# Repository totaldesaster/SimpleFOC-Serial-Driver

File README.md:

# SimpleFOC-Serial-Driver
Advanced dual BLDC driver modules, designed to be controlled from a trajectory controller over a serial connection. Features a compact high power design with two stacked PCBs. While the top PCB focuses on motor driving, the bottom PCB serves as the controller and interface board.

Work in Progress, will be updated as more information and tests become available!

# Base Board (RP2350)

The base board acts as a carrier for power boards and contains the microcontroller, communications and programming interfaces, and power input circuits. It shares power with top-mounted driver boards over the standoffs in the mounting holes. It's equipped with:  

- RP2354B, Dual Cortex-M33 or RISC-V processors at 150MHz
- THVD1424, communication over RS-485 or RS-422 at up to 10MHz
- Input voltage and current monitoring
- Two Encoder connections with I2C interfaces
- External connections to power, RS-422/485 and TTL UART

# Dual BLDC driver board

Featuring two BLDC drivers and an auxiliary circuit to dissipate braking energy, the Dual BLDC board is able to drive low to medium power BLDCs at up to 7 amps. Peak currents may be far higher (not yet tested).  

- Two DRV8323S (SPI configuration) or DRV8323H (hard-coded) BLDC drivers
- Medium-Power HSBB6066 MOSFETs
- Onboard brake resistor able to dissipate ~5 watts
- Onboard thermistor to measure the board's temperature

# High-Power BLDC driver board

Equipped with bigger MOSFETs and connection points for an external brake resistor and power supply, this board is able to drive a much higher power motor.  

- DRV8323S BLDC driver
- 160A rated Infineon OptiMOS MOSFETs, continuous power limited by thermals (not yet tested)$
- Auxiliary output for external brake resistor
- Onboard thermistor to measure the board's temperature

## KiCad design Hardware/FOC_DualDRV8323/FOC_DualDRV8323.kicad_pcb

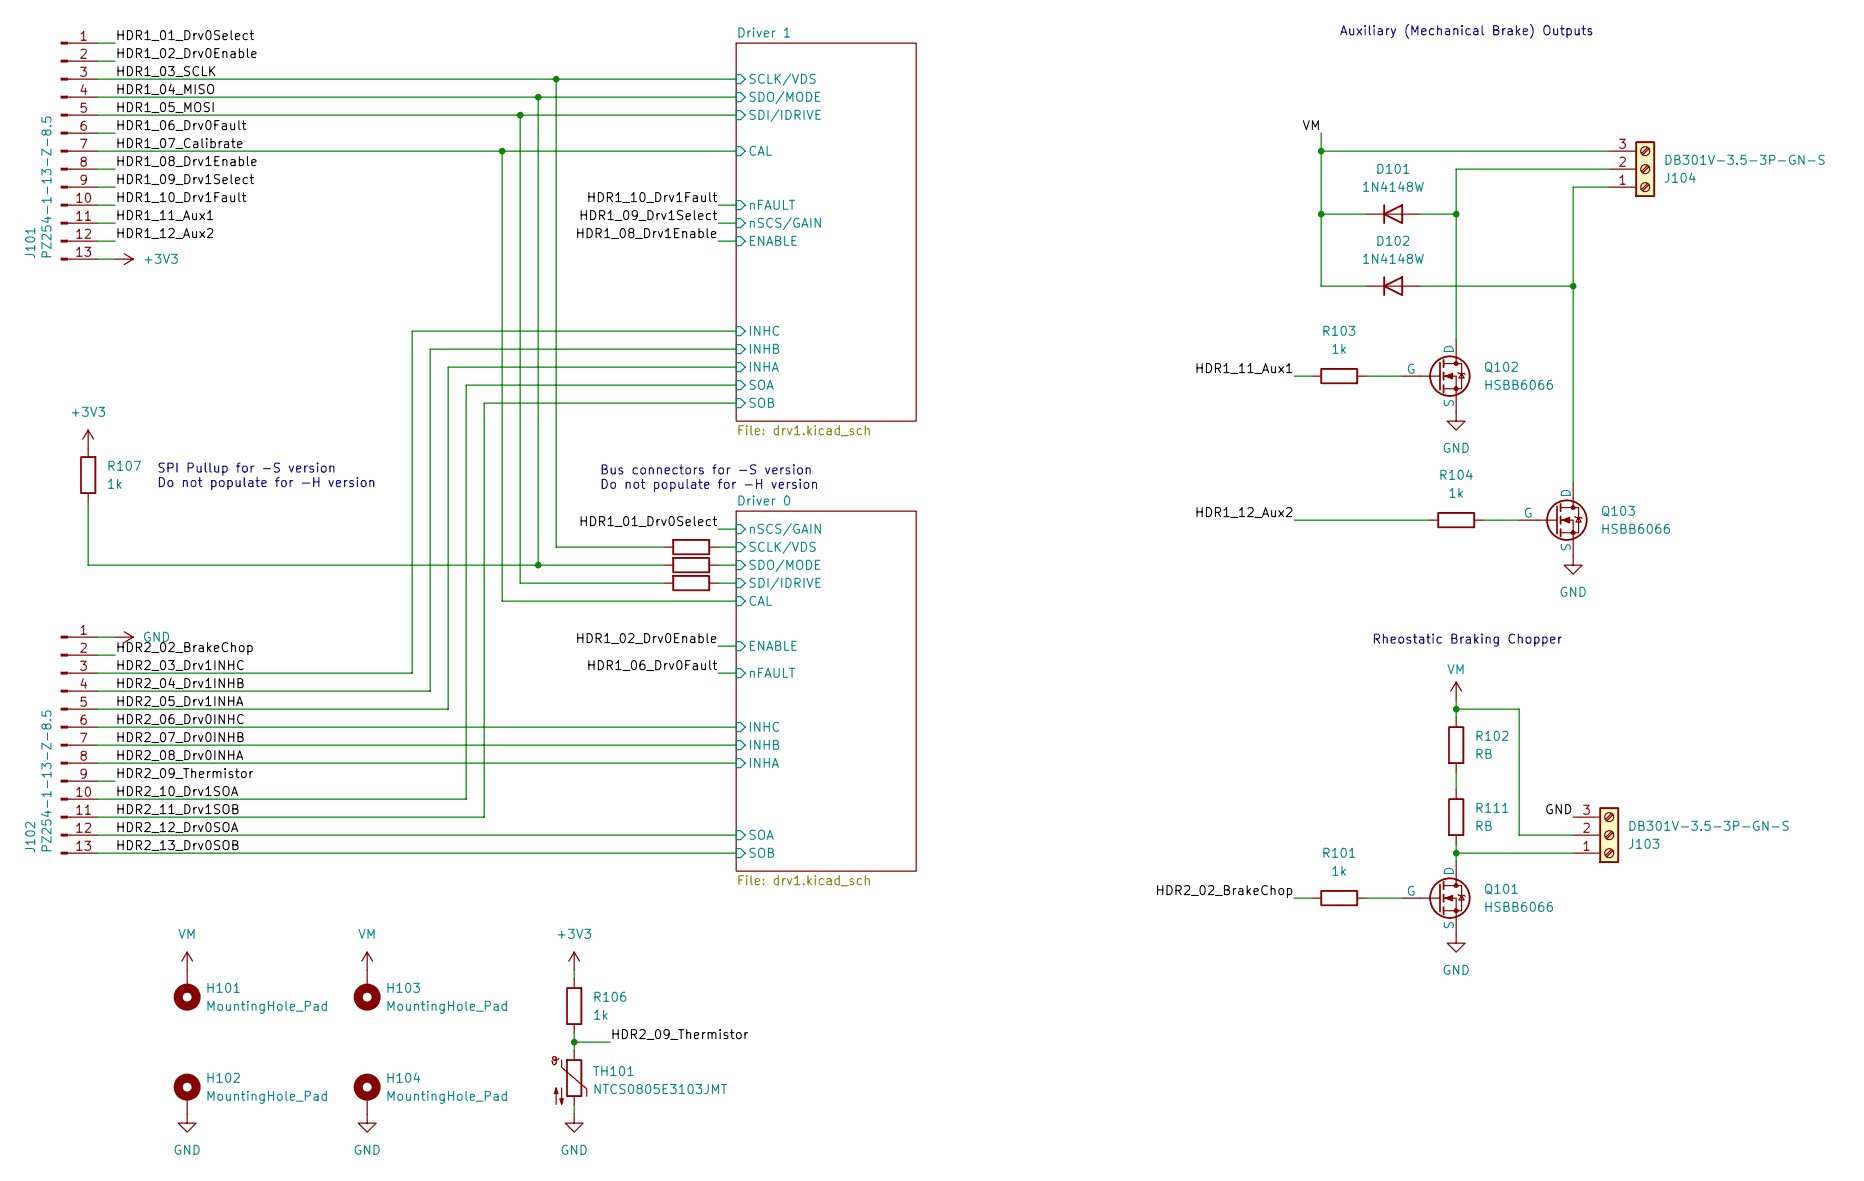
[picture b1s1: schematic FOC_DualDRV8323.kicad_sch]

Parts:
D101, D102: 1N4148W; D_SOD-123
H101, H102, H103, H104: MountingHole_Pad; MountingHole_3.2mm_M3_Pad_Via
J101: PZ254-1-13-Z-8.5; PinHeader_1x13_P2.54mm_Vertical_SMD_Pin1Left
J102: PZ254-1-13-Z-8.5; PinHeader_1x13_P2.54mm_Vertical_SMD_Pin1Right
J103, J104: DB301V-3.5-3P-GN-S; TerminalBlock_Phoenix_PT-1,5-3-3.5-H_1x03_P3.50mm_Horizontal
Q101, Q102, Q103: HSBB6066; VSON-8_3.3x3.3mm_P0.65mm_NexFET
R101, R103, R104, R106, R107: 1k; R_0603_1608Metric
R102, R111: RB; R_Axial_DIN0414_L11.9mm_D4.5mm_P15.24mm_Horizontal
R108, R109, R110: 0; R_0603_1608Metric
TH101: NTCS0805E3103JMT; R_0805_2012Metric

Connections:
+3V3: J101.13, R106.2, R107.2
/Driver 0/SCLK/VDS: R108.1; also elsewhere on the board
/Driver 0/SDI/IDRIVE: R110.1; also elsewhere on the board
/Driver 0/SDO/MODE: R109.1; also elsewhere on the board
/HDR1_01_Drv0Select: J101.1; also elsewhere on the board
/HDR1_02_Drv0Enable: J101.2; also elsewhere on the board
/HDR1_03_SCLK: J101.3, R108.2; also elsewhere on the board
/HDR1_04_MISO: J101.4, R107.1, R109.2; also elsewhere on the board
/HDR1_05_MOSI: J101.5, R110.2; also elsewhere on the board
/HDR1_06_Drv0Fault: J101.6; also elsewhere on the board
/HDR1_07_Calibrate: J101.7; also elsewhere on the board
/HDR1_08_Drv1Enable: J101.8; also elsewhere on the board
/HDR1_09_Drv1Select: J101.9; also elsewhere on the board
/HDR1_10_Drv1Fault: J101.10; also elsewhere on the board
/HDR1_11_Aux1: J101.11, R103.1
/HDR1_12_Aux2: J101.12, R104.1
/HDR2_02_BrakeChop: J102.2, R101.1
/HDR2_03_Drv1INHC: J102.3; also elsewhere on the board
/HDR2_04_Drv1INHB: J102.4; also elsewhere on the board
/HDR2_05_Drv1INHA: J102.5; also elsewhere on the board
/HDR2_06_Drv0INHC: J102.6; also elsewhere on the board
/HDR2_07_Drv0INHB: J102.7; also elsewhere on the board
/HDR2_08_Drv0INHA: J102.8; also elsewhere on the board
/HDR2_09_Thermistor: J102.9, R106.1, TH101.1
/HDR2_10_Drv1SOA: J102.10; also elsewhere on the board
/HDR2_11_Drv1SOB: J102.11; also elsewhere on the board
/HDR2_12_Drv0SOA: J102.12; also elsewhere on the board
/HDR2_13_Drv0SOB: J102.13; also elsewhere on the board
GND: H102.1 (1_1), H104.1 (1_1), J102.1, J103.3, Q101.3 (S), Q102.3 (S), Q103.3 (S), TH101.2; also elsewhere on the board
unnamed: D101.2 (A), J104.2, Q102.1 (D)
unnamed: D102.2 (A), J104.1, Q103.1 (D)
unnamed: J103.1, Q101.1 (D), R111.2
unnamed: Q101.2 (G), R101.2
unnamed: Q102.2 (G), R103.2
unnamed: Q103.2 (G), R104.2
unnamed: R102.2, R111.1
VM: D101.1 (K), D102.1 (K), H101.1 (1_1), H103.1 (1_1), J103.2, J104.3, R102.1; also elsewhere on the board

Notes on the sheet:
Rheostatic Braking Chopper
Bus connectors for -S version Do not populate for -H version
Auxiliary (Mechanical Brake) Outputs
SPI Pullup for -S version Do not populate for -H version

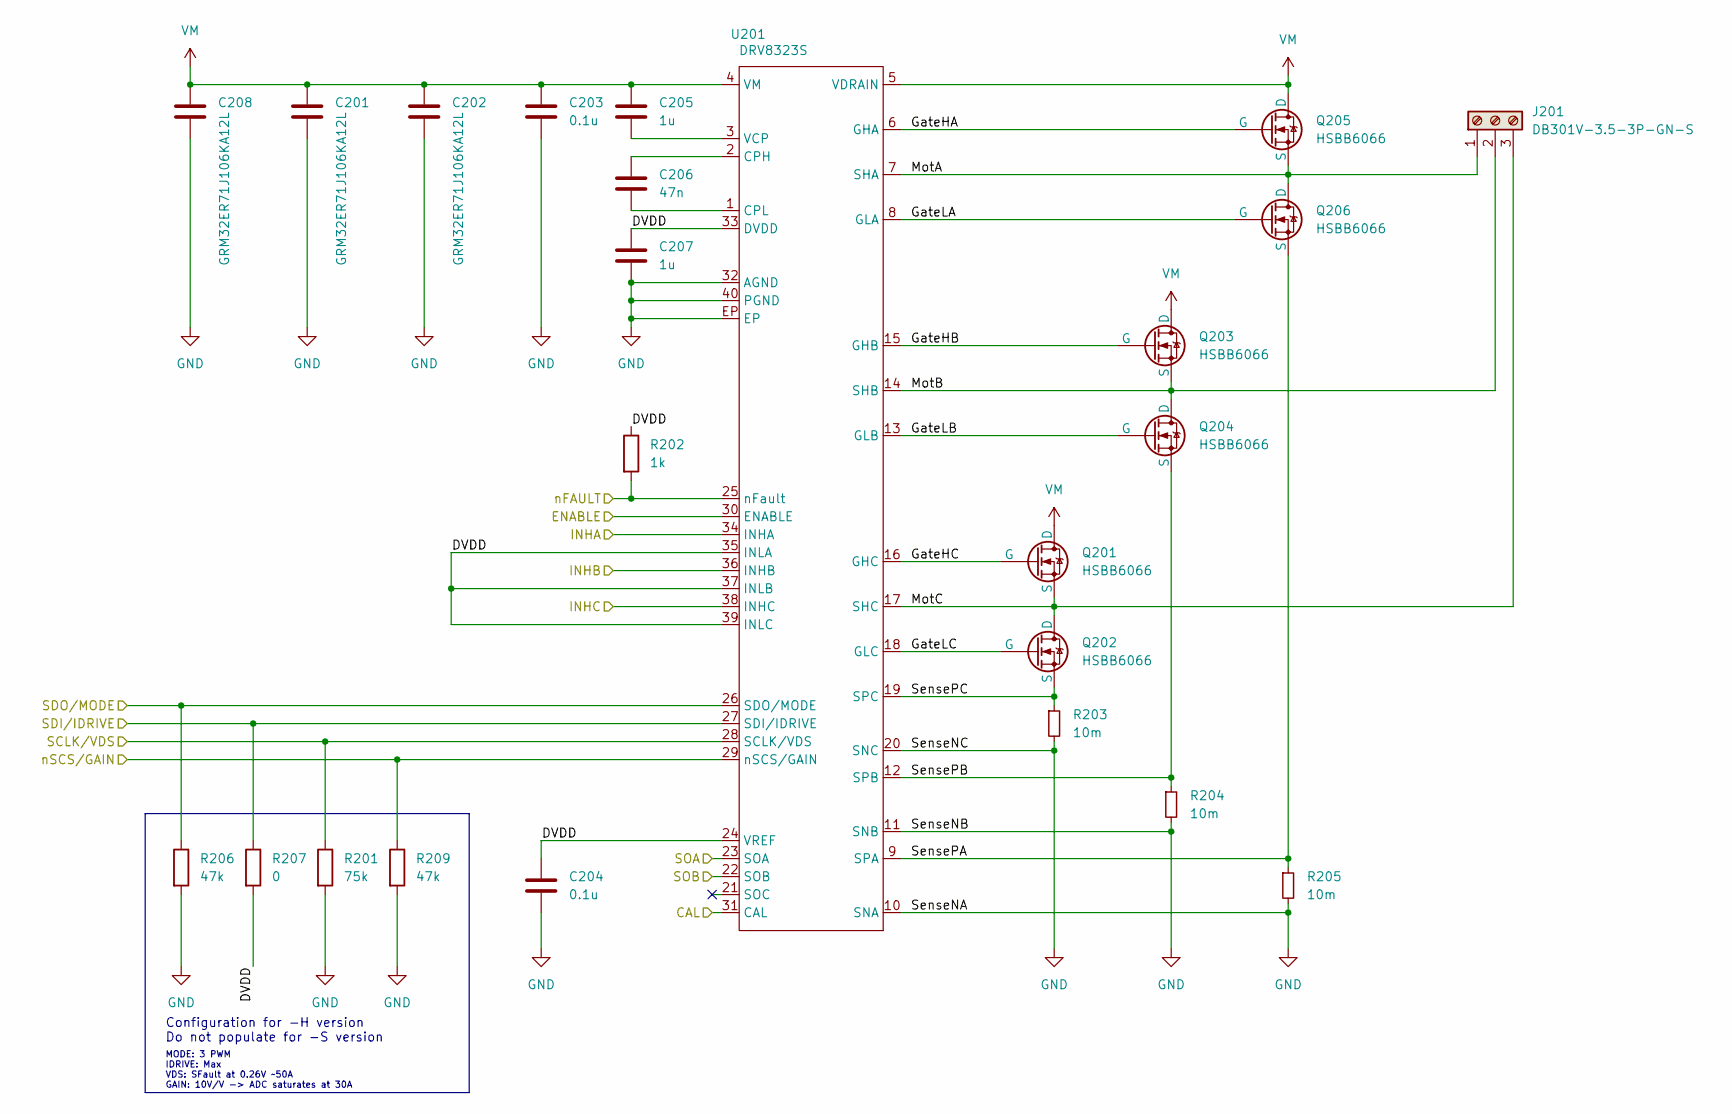
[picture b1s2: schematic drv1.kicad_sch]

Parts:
C201, C202, C208: GRM32ER71J106KA12L; C_1210_3225Metric
C203, C204: 0.1u; C_0603_1608Metric
C205, C207: 1u; C_0603_1608Metric
C206: 47n; C_0603_1608Metric
J201: DB301V-3.5-3P-GN-S; TerminalBlock_Phoenix_PT-1,5-3-3.5-H_1x03_P3.50mm_Horizontal
Q201, Q202, Q203, Q204, Q205, Q206: HSBB6066; VSON-8_3.3x3.3mm_P0.65mm_NexFET
R201: 75k; R_0603_1608Metric
R202: 1k; R_0603_1608Metric
R203, R204, R205: 10m; R_1206_3216Metric
R206, R209: 47k; R_0603_1608Metric
R207: 0; R_0603_1608Metric
U201: DRV8323S; Texas_RHA0040E_VQFN-40-1EP_6x6mm_P0.5mm_EP3.52x2.62mm

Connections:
/Driver 0/DVDD: C204.1, C207.1, R202.1, R207.2, U201.24 (VREF), U201.33 (DVDD), U201.35 (INLA), U201.37 (INLB), U201.39 (INLC)
/Driver 0/GateHA: Q205.2 (G), U201.6 (GHA)
/Driver 0/GateHB: Q203.2 (G), U201.15 (GHB)
/Driver 0/GateHC: Q201.2 (G), U201.16 (GHC)
/Driver 0/GateLA: Q206.2 (G), U201.8 (GLA)
/Driver 0/GateLB: Q204.2 (G), U201.13 (GLB)
/Driver 0/GateLC: Q202.2 (G), U201.18 (GLC)
/Driver 0/MotA: J201.1, Q205.3 (S), Q206.1 (D), U201.7 (SHA)
/Driver 0/MotB: J201.2, Q203.3 (S), Q204.1 (D), U201.14 (SHB)
/Driver 0/MotC: J201.3, Q201.3 (S), Q202.1 (D), U201.17 (SHC)
/Driver 0/SCLK/VDS: R201.1, U201.28 (SCLK/VDS); also elsewhere on the board
/Driver 0/SDI/IDRIVE: R207.1, U201.27 (SDI/IDRIVE); also elsewhere on the board
/Driver 0/SDO/MODE: R206.1, U201.26 (SDO/MODE); also elsewhere on the board
/Driver 0/SensePA: Q206.3 (S), R205.1, U201.9 (SPA)
/Driver 0/SensePB: Q204.3 (S), R204.1, U201.12 (SPB)
/Driver 0/SensePC: Q202.3 (S), R203.1, U201.19 (SPC)
/HDR1_01_Drv0Select: R209.1, U201.29 (nSCS/GAIN); also elsewhere on the board
/HDR1_02_Drv0Enable: U201.30 (ENABLE); also elsewhere on the board
/HDR1_06_Drv0Fault: R202.2, U201.25 (nFault); also elsewhere on the board
/HDR1_07_Calibrate: U201.31 (CAL); also elsewhere on the board
/HDR2_06_Drv0INHC: U201.38 (INHC); also elsewhere on the board
/HDR2_07_Drv0INHB: U201.36 (INHB); also elsewhere on the board
/HDR2_08_Drv0INHA: U201.34 (INHA); also elsewhere on the board
/HDR2_12_Drv0SOA: U201.23 (SOA); also elsewhere on the board
/HDR2_13_Drv0SOB: U201.22 (SOB); also elsewhere on the board
GND: C201.2, C202.2, C203.2, C204.2, C207.2, C208.2, R201.2, R203.2, R204.2, R205.2, R206.2, R209.2, U201.10 (SNA), U201.11 (SNB), U201.20 (SNC), U201.32 (AGND), U201.40 (PGND), U201.EP; also elsewhere on the board
unnamed: C206.1, U201.2 (CPH)
unnamed: C206.2, U201.1 (CPL)
unnamed: C205.2, U201.3 (VCP)
VM: C201.1, C202.1, C203.1, C205.1, C208.1, Q201.1 (D), Q203.1 (D), Q205.1 (D), U201.4 (VM), U201.5 (VDRAIN); also elsewhere on the board

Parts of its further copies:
C301, C302, C308: GRM32ER71J106KA12L; C_1210_3225Metric
C303, C304: 0.1u; C_0603_1608Metric
C305, C307: 1u; C_0603_1608Metric
C306: 47n; C_0603_1608Metric
J301: DB301V-3.5-3P-GN-S; TerminalBlock_Phoenix_PT-1,5-3-3.5-H_1x03_P3.50mm_Horizontal
Q301, Q302, Q303, Q304, Q305, Q306: HSBB6066; VSON-8_3.3x3.3mm_P0.65mm_NexFET
R301: 75k; R_0603_1608Metric
R302: 1k; R_0603_1608Metric
R303, R304, R305: 10m; R_1206_3216Metric
R306, R309: 47k; R_0603_1608Metric
R307: 0; R_0603_1608Metric
U301: DRV8323S; Texas_RHA0040E_VQFN-40-1EP_6x6mm_P0.5mm_EP3.52x2.62mm

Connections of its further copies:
/Driver 1/DVDD: C304.1, C307.1, R302.1, R307.2, U301.24 (VREF), U301.33 (DVDD), U301.35 (INLA), U301.37 (INLB), U301.39 (INLC)
/Driver 1/GateHA: Q305.2 (G), U301.6 (GHA)
/Driver 1/GateHB: Q303.2 (G), U301.15 (GHB)
/Driver 1/GateHC: Q301.2 (G), U301.16 (GHC)
/Driver 1/GateLA: Q306.2 (G), U301.8 (GLA)
/Driver 1/GateLB: Q304.2 (G), U301.13 (GLB)
/Driver 1/GateLC: Q302.2 (G), U301.18 (GLC)
/Driver 1/MotA: J301.1, Q305.3 (S), Q306.1 (D), U301.7 (SHA)
/Driver 1/MotB: J301.2, Q303.3 (S), Q304.1 (D), U301.14 (SHB)
/Driver 1/MotC: J301.3, Q301.3 (S), Q302.1 (D), U301.17 (SHC)
/Driver 1/SensePA: Q306.3 (S), R305.1, U301.9 (SPA)
/Driver 1/SensePB: Q304.3 (S), R304.1, U301.12 (SPB)
/Driver 1/SensePC: Q302.3 (S), R303.1, U301.19 (SPC)
/HDR1_03_SCLK: R301.1, U301.28 (SCLK/VDS); also elsewhere on the board
/HDR1_04_MISO: R306.1, U301.26 (SDO/MODE); also elsewhere on the board
/HDR1_05_MOSI: R307.1, U301.27 (SDI/IDRIVE); also elsewhere on the board
/HDR1_07_Calibrate: U301.31 (CAL); also elsewhere on the board
/HDR1_08_Drv1Enable: U301.30 (ENABLE); also elsewhere on the board
/HDR1_09_Drv1Select: R309.1, U301.29 (nSCS/GAIN); also elsewhere on the board
/HDR1_10_Drv1Fault: R302.2, U301.25 (nFault); also elsewhere on the board
/HDR2_03_Drv1INHC: U301.38 (INHC); also elsewhere on the board
/HDR2_04_Drv1INHB: U301.36 (INHB); also elsewhere on the board
/HDR2_05_Drv1INHA: U301.34 (INHA); also elsewhere on the board
/HDR2_10_Drv1SOA: U301.23 (SOA); also elsewhere on the board
/HDR2_11_Drv1SOB: U301.22 (SOB); also elsewhere on the board
GND: C301.2, C302.2, C303.2, C304.2, C307.2, C308.2, R301.2, R303.2, R304.2, R305.2, R306.2, R309.2, U301.10 (SNA), U301.11 (SNB), U301.20 (SNC), U301.32 (AGND), U301.40 (PGND); also elsewhere on the board
unnamed: C306.1, U301.2 (CPH)
unnamed: C306.2, U301.1 (CPL)
unnamed: C305.2, U301.3 (VCP)
VM: C301.1, C302.1, C303.1, C305.1, C308.1, Q301.1 (D), Q303.1 (D), Q305.1 (D), U301.4 (VM), U301.5 (VDRAIN); also elsewhere on the board

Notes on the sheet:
Configuration for -H version Do not populate for -S version
MODE: 3 PWM IDRIVE: Max VDS: SFault at 0.26V ~50A GAIN: 10V/V -> ADC saturates at 30A

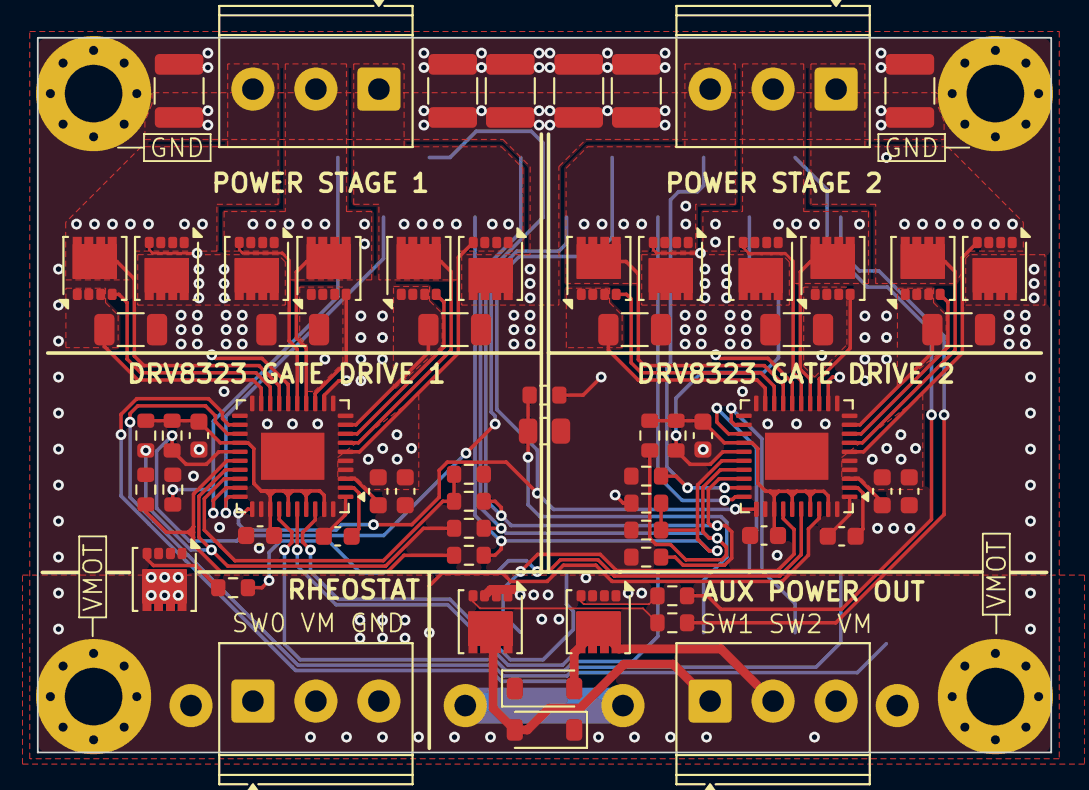
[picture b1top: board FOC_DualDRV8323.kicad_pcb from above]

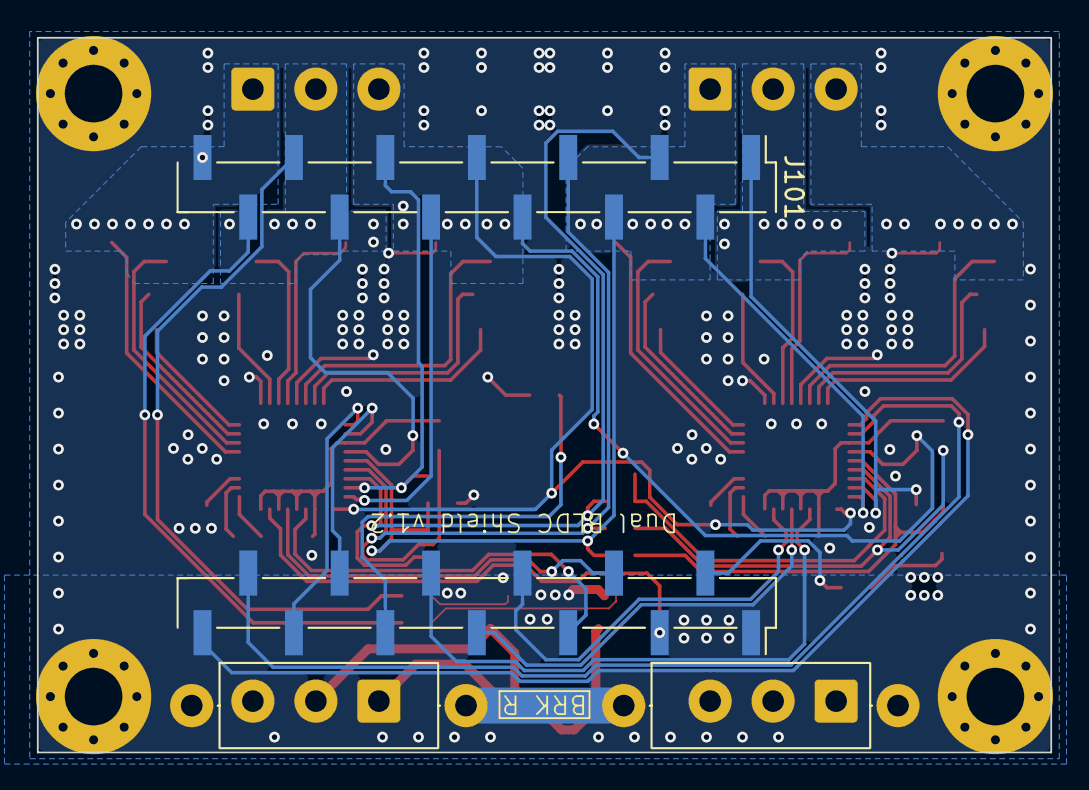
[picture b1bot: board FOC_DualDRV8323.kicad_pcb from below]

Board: 4 copper layers, 56.3 x 39.7 mm, 72 parts (4 on the bottom side), 69 nets.

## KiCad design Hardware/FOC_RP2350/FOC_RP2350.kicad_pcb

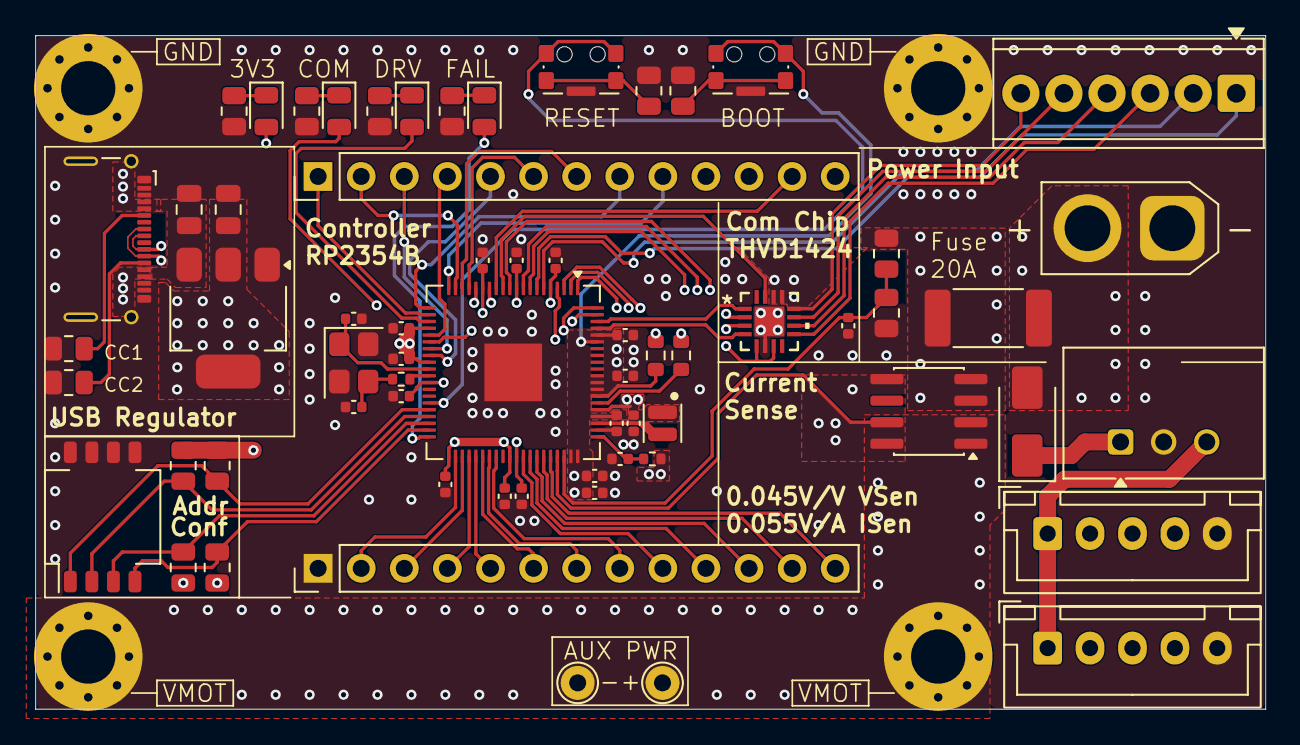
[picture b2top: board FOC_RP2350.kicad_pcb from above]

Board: 4 copper layers, 72.5 x 39.7 mm, 68 parts (0 on the bottom side), 78 nets.

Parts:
C201, C202, C203, C204, C205, C206, C208, C209, C211, C213, C214, C215, C216: 100n; C_0402_1005Metric
C207, C210, C212, C403: 4.7u; C_0402_1005Metric
C217, C218: 15p; C_0402_1005Metric
C401, C402: 22u; C_0805_2012Metric
D301, D302, D303: KT-0805G; LED_0805_2012Metric
D304: KT-0805R; LED_0805_2012Metric
D401: SS12; D_SMA
F401: BSMD2410C-2200T; Fuse_2512_6332Metric_Pad1.52x3.35mm_HandSolder
H401, H402, H403, H404: MountingHole_Pad; MountingHole_3.2mm_M3_Pad_Via
H405, H406: MountingHole_Pad; TestPoint_THTPad_D2.0mm_Drill1.0mm
J401: GT-USB-7025; USB_C_Receptacle_G-Switch_GT-USB-7025
J402: DB125-2.54-6P-GN-S; TerminalBlock_Phoenix_MPT-0,5-6-2.54_1x06_P2.54mm_Horizontal
J403, J408: Conn_01x05; JST_XH_B5B-XH-A_1x05_P2.50mm_Vertical
J404: XT30U-M; AMASS_XT30U-F_1x02_P5.0mm_Vertical
J406, J407: PZ254-1-13-Z-8.5; PinHeader_1x13_P2.54mm_Vertical
L201: AOTA-B201610S3R3-101-T; L_Changjiang_FTC201607S
R201: 33; R_0402_1005Metric
R202, R205, R301, R302, R303, R308: 1k; R_0805_2012Metric
R203, R204: 27; R_0603_1608Metric
R206: 1k; R_0402_1005Metric
R304, R305, R306, R307, R401, R402: 5.1k; R_0805_2012Metric
R403: 10k; R_0805_2012Metric
R404: 470; R_0805_2012Metric
SW201, SW202: KMS231GLFS; SW_SPST_CK_KMS2xxGP
SW301: DSHP04TSGER; SW_DIP_SPSTx04_Slide_KingTek_DSHP04TS_W7.62mm_P1.27mm
U201: RP2354B; QFN-80-1EP_10x10mm_P0.4mm_EP3.4x3.4mm
U301: THVD1424RGTR; QFN_24RGTR_TEX
U401: AMS1117-3.3; SOT-223-3_TabPin2
U402: ACS711KLCTR-25AB-T; SOIC-8_3.9x4.9mm_P1.27mm
U403: TSR1-2433E; Converter_DCDC_TRACO_TSR1-xxxxE_THT
Y201: ABM8-272-T3; Crystal_SMD_Abracon_ABM8G-4Pin_3.2x2.5mm

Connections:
/Comms/3V3: C202.1, C204.1, C206.1, C208.1, C209.1, C210.1, C211.1, C213.1, C214.1, C215.1, C216.1, C402.1, D303.2 (A), J403.1, J406.13, J408.1, R201.1, R304.2, R305.2, R306.2, R307.2, U201.5 (IOVDD), U201.15 (IOVDD), U201.24 (IOVDD), U201.29 (IOVDD), U201.41 (IOVDD), U201.50 (IOVDD), U201.59 (ADC_AVDD), U201.60 (IOVDD), U201.64 (VREG_VIN), U201.68 (USB_OTP_VDD), U201.69 (QSPI_IOVDD), U201.76 (IOVDD), U301.13 (VIO), U301.14 (VCC), U401.2 (VO), U402.8 (VCC), U403.3 (Vout)
/Comms/ComBus_HF: U201.12 (GPIO13), U301.15 (H/F)
/Comms/ConfSw_1: R307.1, SW301.1, U201.36 (GPIO28)
/Comms/ConfSw_2: R306.1, SW301.2, U201.37 (GPIO29)
/Comms/ConfSw_3: R305.1, SW301.3, U201.38 (GPIO30)
/Comms/ConfSw_4: R304.1, SW301.4, U201.39 (GPIO31)
/Comms/Led1: D302.2 (A), U201.26 (GPIO25)
/Comms/Led2: D301.2 (A), U201.23 (GPIO23)
/Comms/Led3: D304.2 (A), U201.40 (GPIO32)
/Comms/RS485_A: J402.6, U301.12 (A)
/Comms/RS485_B: J402.5, U301.11 (B)
/Comms/RS485_Y: J402.3, U301.9 (Y)
/Comms/RS485_Z: J402.4, U301.10 (Z)
/Controller/1V1: C201.1, C203.1, C205.1, C207.1, L201.1, U201.10 (DVDD), U201.32 (DVDD), U201.51 (DVDD), U201.65 (VREG_FB)
/Controller/GPIO6: J408.4, U201.3 (GPIO6)
/Controller/GPIO7: J403.4, U201.4 (GPIO7)
/Controller/GPIO14: J406.12, U201.13 (GPIO14)
/Controller/GPIO15: J406.11, U201.14 (GPIO15)
/Controller/GPIO16: J406.10, U201.16 (GPIO16)
/Controller/GPIO17: J406.6, U201.17 (GPIO17)
/Controller/GPIO18: J406.7, U201.18 (GPIO18)
/Controller/GPIO19: J406.2, U201.19 (GPIO19)
/Controller/GPIO22: J406.1, U201.22 (GPIO22)
/GPIO0_UART0_TX: U201.77 (GPIO0), U301.4 (D)
/GPIO1_UART0_RX: U201.78 (GPIO1), U301.1 (R)
/GPIO2_I2C1_SDA: J403.2, U201.79 (GPIO2)
/GPIO3_I2C1_SCL: J403.3, U201.80 (GPIO3)
/GPIO4_I2C0_SDA: J408.2, U201.1 (GPIO4)
/GPIO5_I2C0_SCL: J408.3, U201.2 (GPIO5)
/GPIO8_UART1_TX: J402.2, U201.6 (GPIO8)
/GPIO9_UART1_RX: J402.1, U201.7 (GPIO9)
/GPIO10_TERM: U201.8 (GPIO10), U301.5 (TERM_TX), U301.7 (TERM_RX)
/GPIO11_TXEN: U201.9 (GPIO11), U301.3 (DE)
/GPIO12_RXEN: U201.11 (GPIO12), U301.2 (RE)
/GPIO20_UART1_TX: J406.9, U201.20 (GPIO20)
/GPIO21_UART1_RX: J406.8, U201.21 (GPIO21)
/GPIO24_SPI1_MISO: J406.4, U201.25 (GPIO24)
/GPIO26_SPI1_SCK: J406.3, U201.27 (GPIO26)
/GPIO27_SPI1_MOSI: J406.5, U201.28 (GPIO27)
/GPIO33_PWM8B: J407.2, U201.42 (GPIO33)
/GPIO34_PWM9A: J407.3, U201.43 (GPIO34)
/GPIO35_PWM9B: J407.4, U201.44 (GPIO35)
/GPIO36_PWM10A: J407.5, U201.45 (GPIO36)
/GPIO37_PWM10B: J407.6, U201.46 (GPIO37)
/GPIO38_PWM11A: J407.7, U201.47 (GPIO38)
/GPIO39_PWM11B: J407.8, U201.48 (GPIO39)
/GPIO41_ADC1: J407.9, U201.52 (GPIO41/ADC1)
/GPIO42_ADC2: J407.10, U201.53 (GPIO42/ADC2)
/GPIO43_ADC3: J407.11, U201.54 (GPIO43/ADC3)
/GPIO44_ADC4: J407.12, U201.55 (GPIO44/ADC4)
/GPIO45_ADC5: J407.13, U201.56 (GPIO45/ADC5)
/GPIO46_ADC6: U201.57 (GPIO46/ADC6), U402.7 (VIOUT)
/GPIO47_ADC7: C403.1, R403.1, R404.2, U201.58 (GPIO47/ADC7)
/Power and Connections/USB_VBUS: C401.1, J401.A4 (VBUS), J401.A9 (VBUS), J401.B4 (VBUS), J401.B9 (VBUS), U401.3 (VI)
/Power and Connections/VCON: D401.2 (A), F401.1, J404.2
/Power and Connections/VIN: F401.2, R403.2, U402.3 (IP-), U402.4 (IP-)
/USB_D+: J401.A6 (D+), J401.B6 (D+), R204.1
/USB_D-: J401.A7 (D-), J401.B7 (D-), R203.1
GND: C201.2, C202.2, C203.2, C204.2, C205.2, C206.2, C207.2, C208.2, C209.2, C210.2, C211.2, C212.2, C213.2, C214.2, C215.2, C216.2, C217.2, C218.2, C401.2, C402.2, C403.2, H403.1 (1_1), H404.1 (1_1), H406.1 (1_1), J401.A1 (GND), J401.A12 (GND), J401.B1 (GND), J401.B12 (GND), J401.SH (SHIELD), J403.5, J404.1, J407.1, J408.5, R202.1, R205.1, R301.1, R302.1, R303.1, R308.1, R401.1, R402.1, R404.1, SW201.SH (B), SW202.SH (B), SW301.5, SW301.6, SW301.7, SW301.8, U201.62 (VREG_PGND), U201.81 (GND), U301.6 (GND), U301.17 (GND), U401.1 (GND), U402.5 (GND), U403.2 (GND), Y201.2 (G), Y201.4 (G)
unnamed: C218.1, R206.1, Y201.3
unnamed: D301.1 (K), R302.2
unnamed: D302.1 (K), R303.2
unnamed: D303.1 (K), R301.2
unnamed: D304.1 (K), R308.2
unnamed: D401.1 (K), U403.1 (Vin)
unnamed: J401.A5 (CC1), R402.2
unnamed: J401.B5 (CC2), R401.2
unnamed: R202.2, SW201.1
unnamed: R205.2, SW202.1
unnamed: SW201.2, U201.35 (RUN)
unnamed: R203.2, U201.66 (USB_DM)
unnamed: R204.2, U201.67 (USB_DP)
unnamed: C212.1, R201.2, U201.61 (VREG_AVDD)
unnamed: L201.2, U201.63 (VREG_LX)
unnamed: C217.1, U201.30 (XIN), Y201.1
unnamed: R206.2, U201.31 (XOUT)
unnamed: SW202.2, U201.75 (~QSPI_SS)
VMOT: H401.1 (1_1), H402.1 (1_1), H405.1 (1_1), U402.1 (IP+), U402.2 (IP+)
